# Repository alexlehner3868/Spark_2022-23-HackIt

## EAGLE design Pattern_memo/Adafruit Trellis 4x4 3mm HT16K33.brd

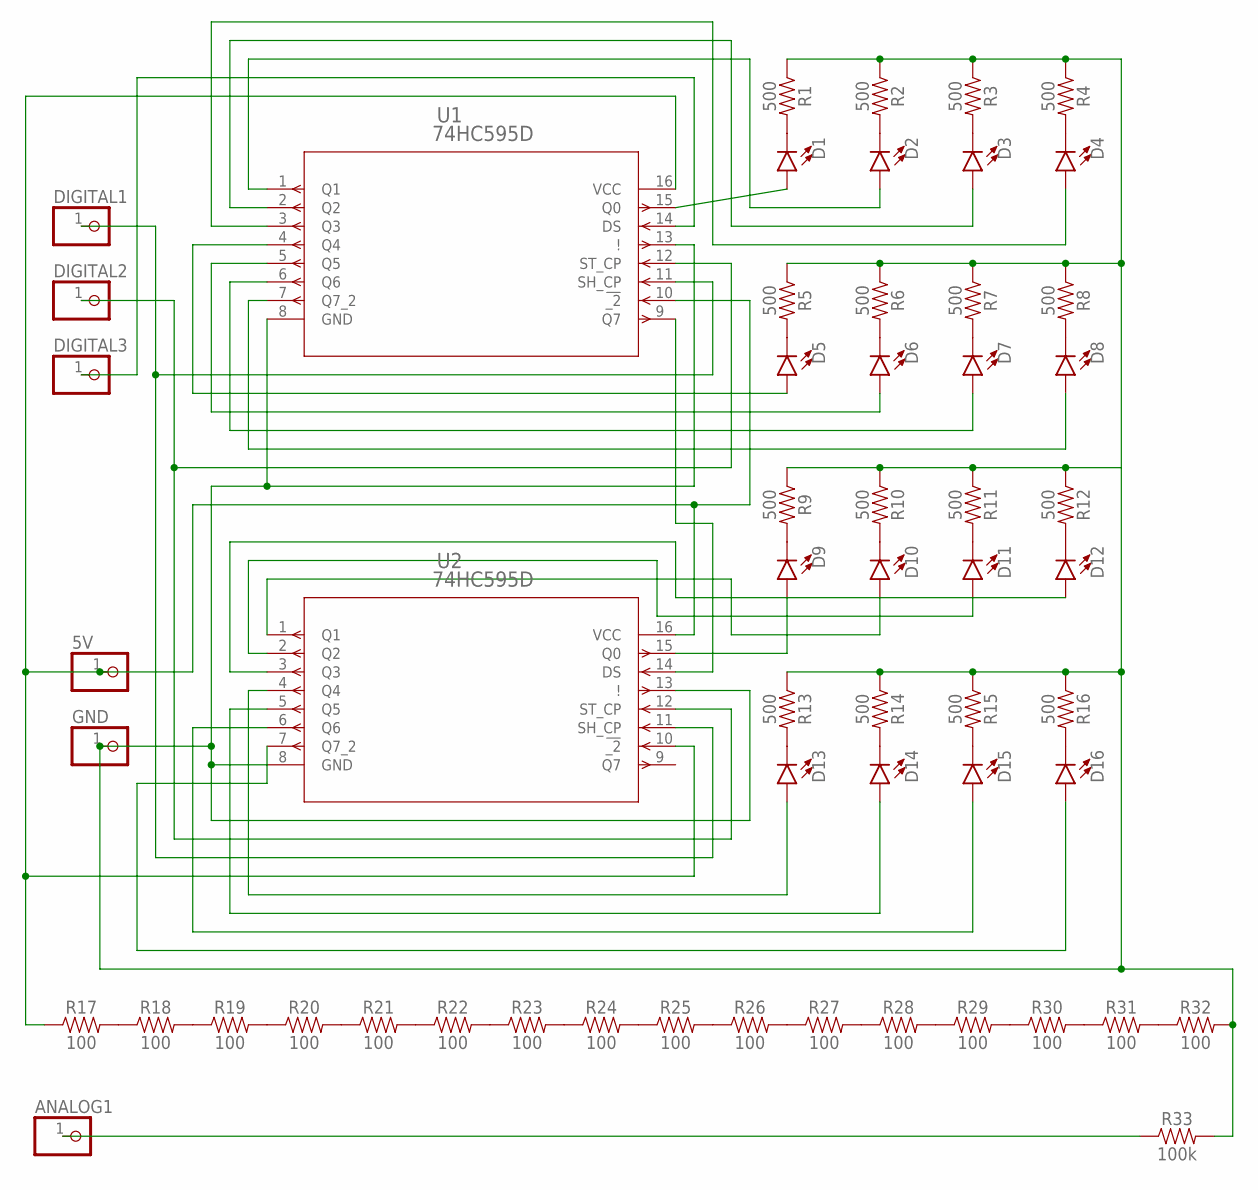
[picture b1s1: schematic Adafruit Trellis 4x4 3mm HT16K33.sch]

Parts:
5V: PINHD-1X1; 1X01
ANALOG1: PINHD-1X1; 1X01
D1, D2, D3, D4, D5, D6, D7, D8, D9, D10, D11, D12, D13, D14, D15, D16: LED3MM; LED_3MM
DIGITAL1, DIGITAL2, DIGITAL3: PINHD-1X1; 1X01
GND: PINHD-1X1; 1X01
R1, R2, R3, R4, R5, R6, R7, R8, R9, R10, R11, R12, R13, R14, R15, R16: 500; 0603
R17, R18, R19, R20, R21, R22, R23, R24, R25, R26, R27, R28, R29, R30, R31, R32: 100; 0603
R33: 100k; 0603
U1, U2: 74HC595D; SOT109-1_NXP

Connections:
unnamed: R17.2, R18.1
unnamed: ANALOG1.1, R33.1
unnamed: DIGITAL3.1, U1.14 (DS)
unnamed: D11.A, U2.2 (Q2)
unnamed: DIGITAL2.1, U1.12 (ST_CP), U2.12 (ST_CP)
unnamed: D1.K (C), R1.2
unnamed: D2.K (C), R2.2
unnamed: GND.1, R1.1, R2.1, R3.1, R4.1, R5.1, R6.1, R7.1, R8.1, R9.1, R10.1, R11.1, R12.1, R13.1, R14.1, R15.1, R16.1, R32.2, R33.2, U1.8 (GND), U1.13 (!), U2.8 (GND), U2.13 (!)
unnamed: D3.K (C), R3.2
unnamed: D4.K (C), R4.2
unnamed: D5.K (C), R5.2
unnamed: D6.K (C), R6.2
unnamed: D7.K (C), R7.2
unnamed: D1.A, U1.15 (Q0)
unnamed: D8.K (C), R8.2
unnamed: D9.K (C), R9.2
unnamed: D10.K (C), R10.2
unnamed: D11.K (C), R11.2
unnamed: D12.K (C), R12.2
unnamed: D13.K (C), R13.2
unnamed: D14.K (C), R14.2
unnamed: D15.K (C), R15.2
unnamed: D16.K (C), R16.2
unnamed: D5.A, U1.4 (Q4)
unnamed: D2.A, U1.1 (Q1)
unnamed: D3.A, U1.2 (Q2)
unnamed: D4.A, U1.3 (Q3)
unnamed: U1.9 (Q7), U2.14 (DS)
unnamed: D6.A, U1.5 (Q5)
unnamed: D7.A, U1.6 (Q6)
unnamed: D8.A, U1.7 (Q7_2)
unnamed: D13.A, U2.4 (Q4)
unnamed: D10.A, U2.1 (Q1)
unnamed: 5V.1, R17.1, U1.10 (!_2), U1.16 (VCC), U2.10 (!_2), U2.16 (VCC)
unnamed: D12.A, U2.3 (Q3)
unnamed: R18.2, R19.1
unnamed: D9.A, U2.15 (Q0)
unnamed: D14.A, U2.5 (Q5)
unnamed: R19.2, R20.1
unnamed: D15.A, U2.6 (Q6)
unnamed: R20.2, R21.1
unnamed: R21.2, R22.1
unnamed: R22.2, R23.1
unnamed: R23.2, R24.1
unnamed: R24.2, R25.1
unnamed: R25.2, R26.1
unnamed: R26.2, R27.1
unnamed: R27.2, R28.1
unnamed: R28.2, R29.1
unnamed: R29.2, R30.1
unnamed: R30.2, R31.1
unnamed: R31.2, R32.1
unnamed: D16.A, U2.7 (Q7_2)
unnamed: DIGITAL1.1, U1.11 (SH_CP), U2.11 (SH_CP)

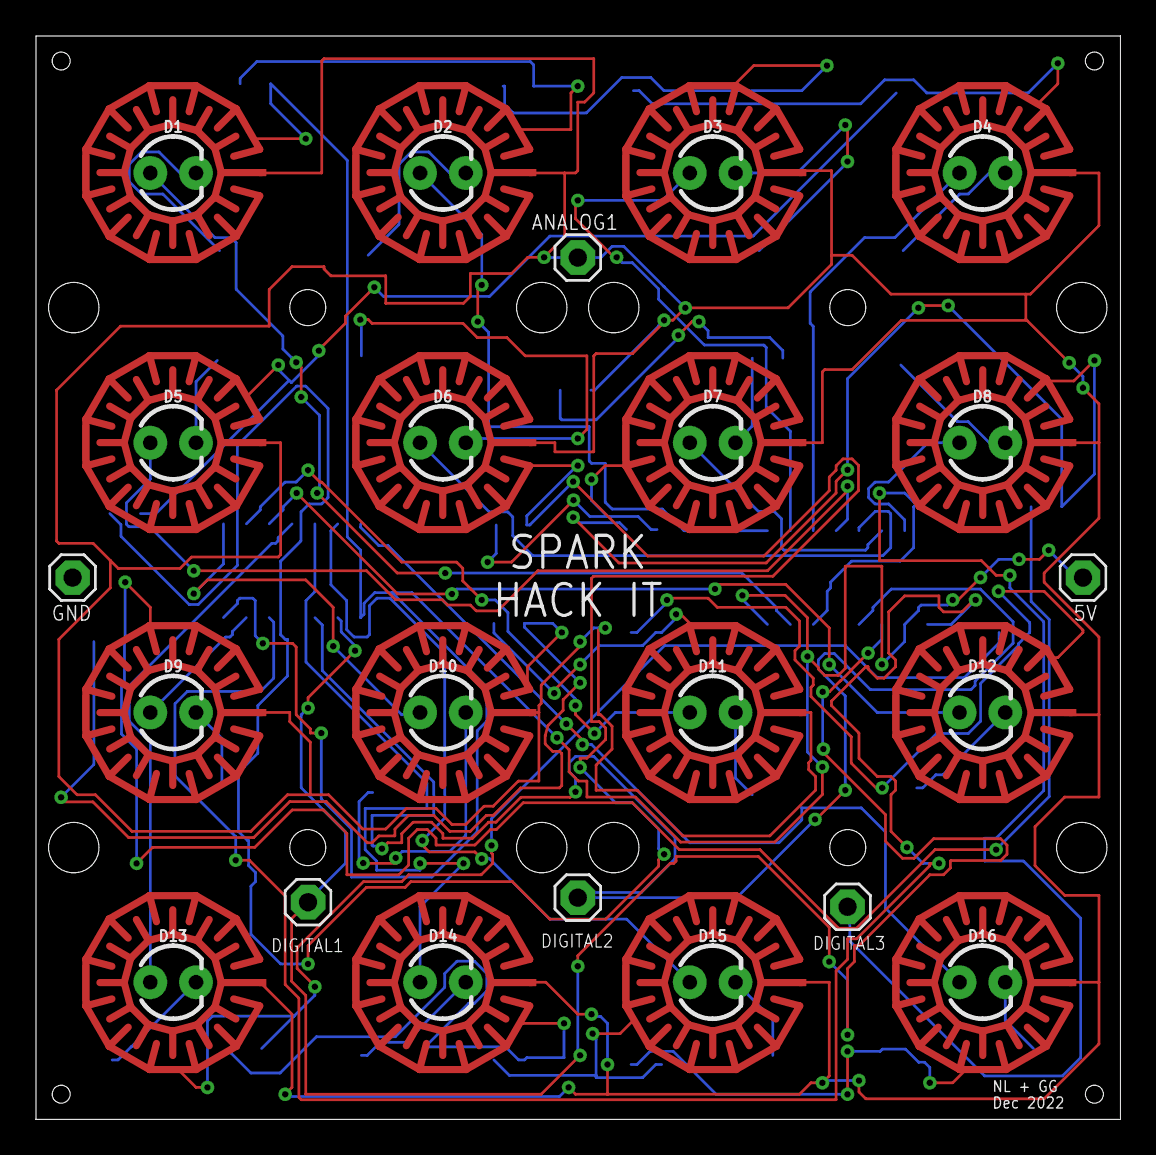
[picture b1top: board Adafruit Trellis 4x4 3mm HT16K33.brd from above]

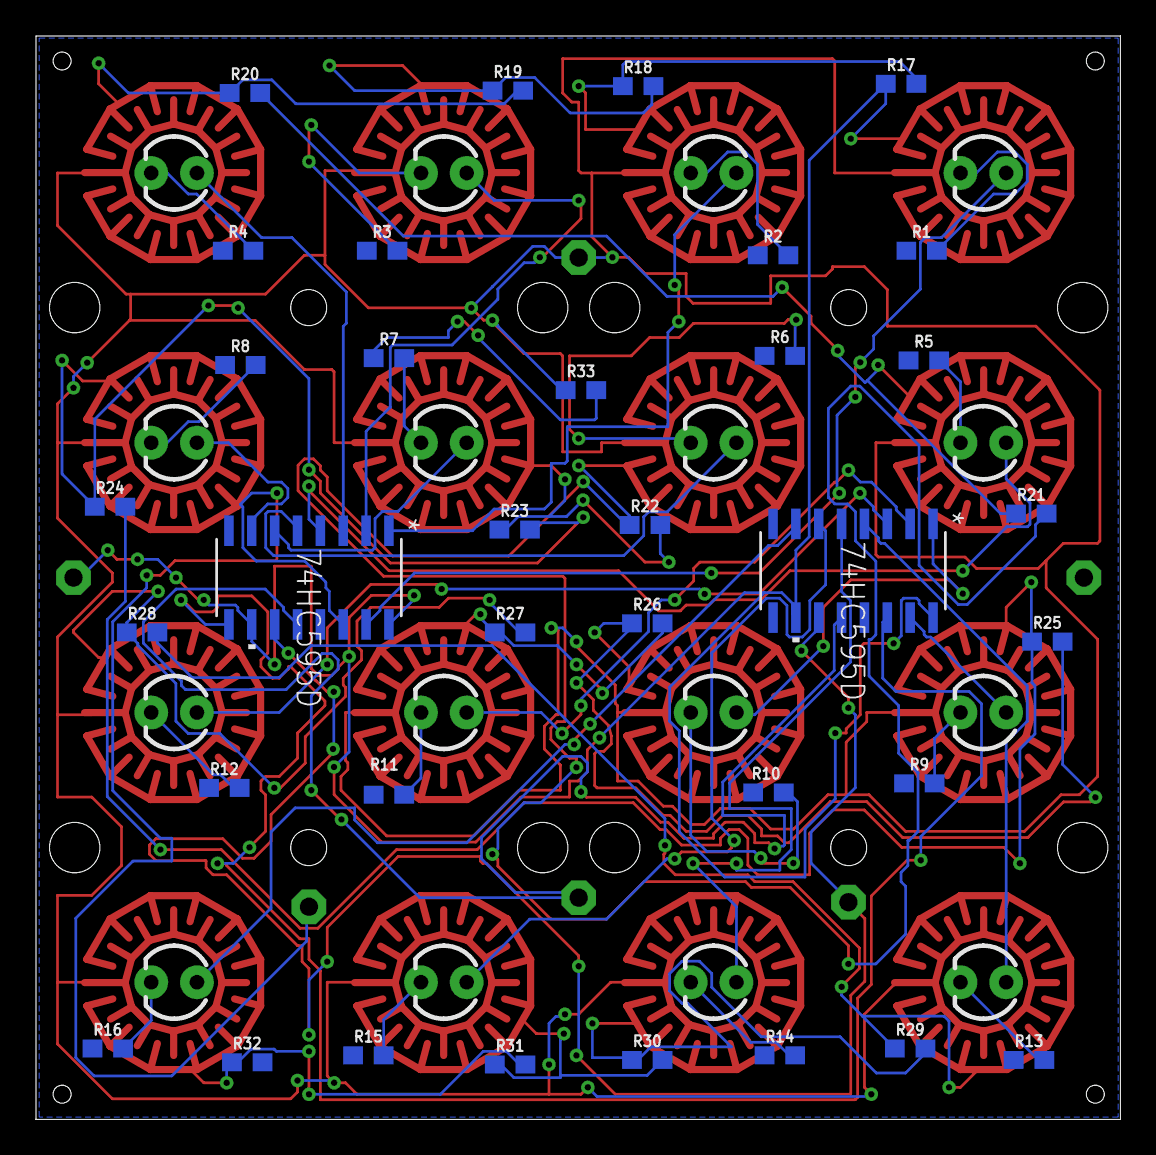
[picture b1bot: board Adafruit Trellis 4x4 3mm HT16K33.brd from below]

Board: 2 copper layers, 60.2 x 60.2 mm, 58 parts (35 on the bottom side), 54 nets.

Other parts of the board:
E$1: ELAST_PAD_SQUARE_10MM_5.4MM_4X4GRID

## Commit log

2022-10-08 create copy-it file
2022-10-22 Update Pattern_memo.ino
    Added createRandomPattern() function. Testing print statements are in comments.
2022-11-05 Added new file for follower arduino
2022-11-05 Added to follower arduino code
2022-11-05 Minor change
2022-11-14 Create Copy_it folder
2022-11-20 pcb design files
2022-11-25 Update Pattern_memo.ino
    Updated beginPattern(), checkPattern(), readInput().
    Created nextLevel(), inRange().
2022-11-26 Initial commit for Click at the Right Time
2022-11-26 initial cart commit
2022-11-26 Added pattern sequences
2022-11-26 updated pcb board
2022-12-02 schematic & board finished
2022-12-03 re-stole code
2022-12-03 move
2022-12-03 Increase speed for CART subgame after each input
2022-12-03 Add structure
2022-12-03 Add structure pt 2
2022-12-03 Add structure pt 3
2022-12-03 fixed errors in PCB board
2022-12-09 Update Copy_It.ino
    Added three new patterns.
2023-01-05 Create 2 grids and image output functions
2023-01-08 Added joystick code
2023-01-08 Put code in right file
2023-01-08 test
2023-01-20 implemented point reduction when player lets LED pass over target without pressing
2023-01-20 completed some functions
2023-01-21 Updated functions
2023-01-27 Added scoring functionality based on player mistakes
2023-01-27 implemented scoring
2023-02-04 Reimplement Copy_it setLED and show_image function
2023-02-04 Rename Copy_it pins
2023-02-11 Implement Copy_it flashing and color change
2023-02-11 pcb circuit test codes
2023-02-11 change pattern to 0-7
2023-03-18 demo test
2023-03-25 Large changes to Copy_it
2023-03-25 Attempt to fix joystick movement
2023-04-01 Implement proper LED flashing and joystick movement
2023-08-26 Implement limit switch cart.ino
2023-08-26 Prevent holding button on cart.ino
2023-08-26 added buzzer noises to hit, win and lose. Game might still be too hard to win in the 30 second time frame with current precision.
2023-08-26 fixed eternal win jingle

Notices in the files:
parts and their libraries:
SparkFun-Resistors: Licensing: Creative Commons ShareAlike 4.0 International - https://creativecommons.org/licenses/by-sa/4.0
COPYRIGHT: Copyright (C) 2022 Ultra Librarian. All rights reserved.
